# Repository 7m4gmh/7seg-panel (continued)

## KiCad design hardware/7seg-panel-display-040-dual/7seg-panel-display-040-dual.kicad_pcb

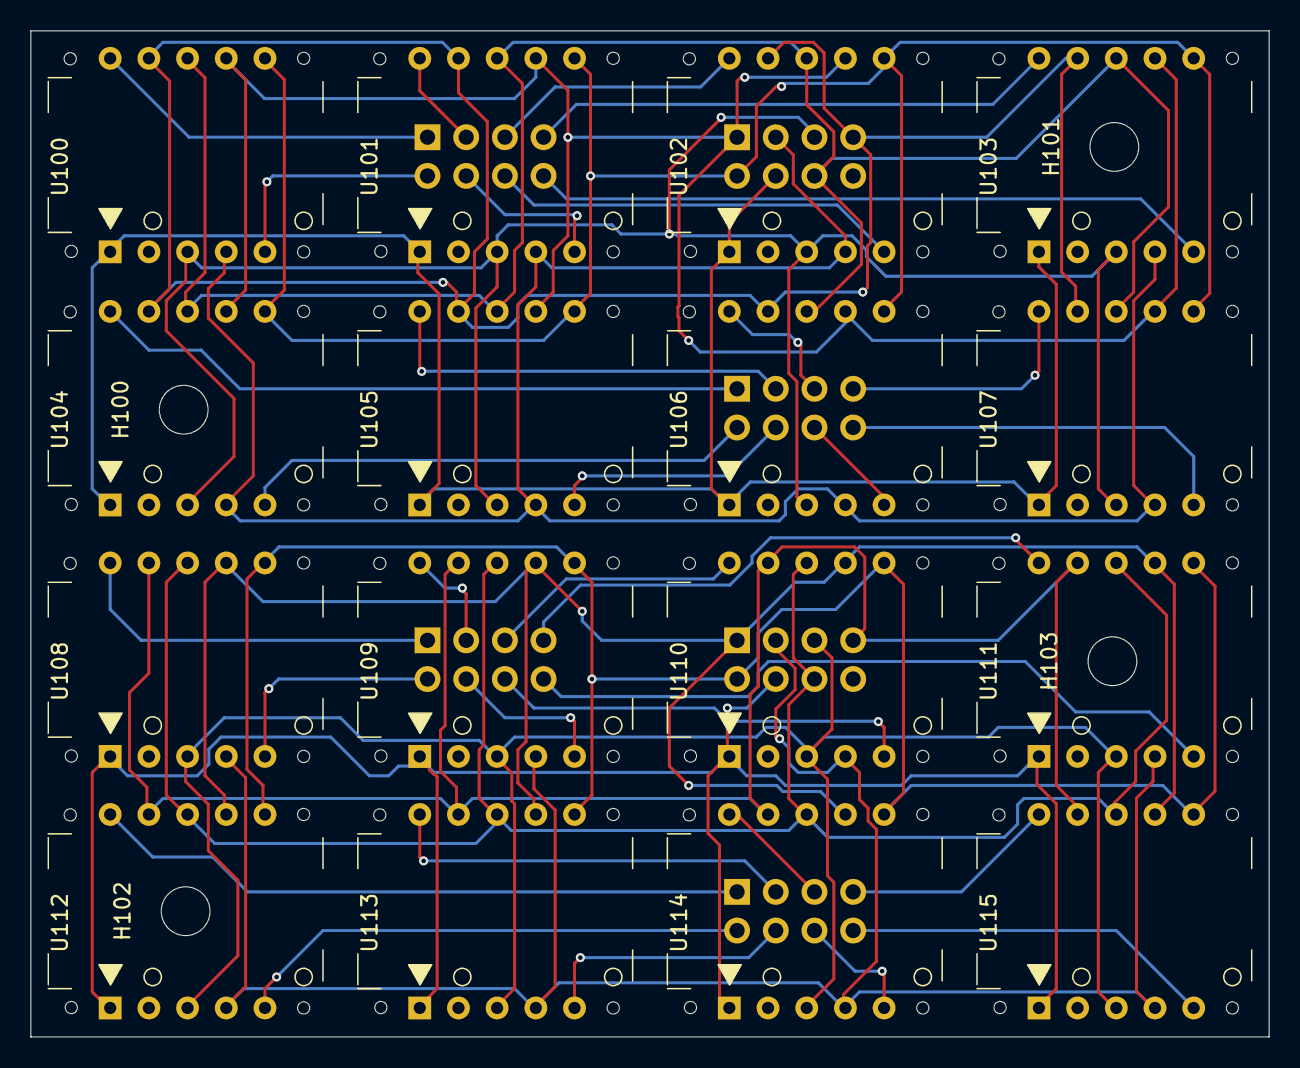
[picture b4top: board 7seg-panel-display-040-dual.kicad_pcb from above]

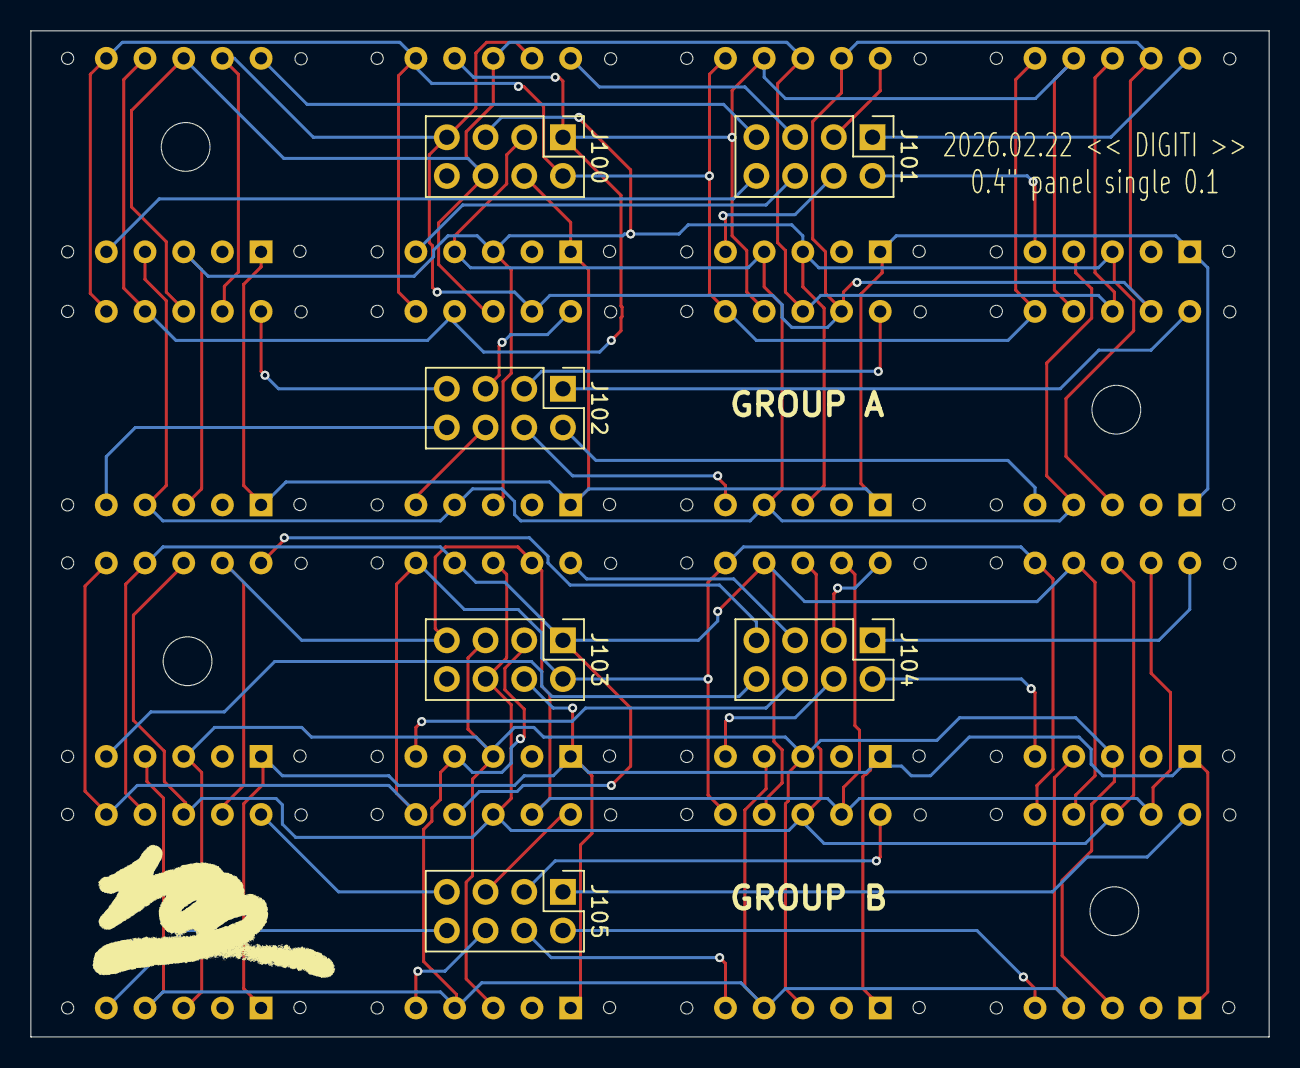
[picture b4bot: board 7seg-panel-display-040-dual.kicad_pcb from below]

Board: 2 copper layers, 81.3 x 66.0 mm, 26 parts (6 on the bottom side), 46 nets.

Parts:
H100, H101, H102, H103: MountingHole; MountingHole_3.2mm_M3
J100, J101, J102, J103, J104, J105: Conn_02x04_Odd_Even; PinHeader_2x04_P2.54mm_Vertical
U100, U101, U102, U103, U104, U105, U106, U107, U108, U109, U110, U111, U112, U113, U114, U115: YH-2E20402-IK; YH-2E20402-12P

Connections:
A_COM0: J100.1, U100.7 (a), U101.7 (a), U102.7 (a), U103.7 (a), U104.7 (a), U105.7 (a), U106.7 (a), U107.7 (a)
A_COM1: J100.2, U100.6 (b), U101.6 (b), U102.6 (b), U103.6 (b), U104.6 (b), U105.6 (b), U106.6 (b), U107.6 (b)
A_COM2: J100.3, U100.4 (c), U101.4 (c), U102.4 (c), U103.4 (c), U104.4 (c), U105.4 (c), U106.4 (c), U107.4 (c)
A_COM3: J100.4, U100.1 (d), U101.1 (d), U102.1 (d), U103.1 (d), U104.1 (d), U105.1 (d), U106.1 (d), U107.1 (d)
A_COM4: J100.5, U100.3 (e), U101.3 (e), U102.3 (e), U103.3 (e), U104.3 (e), U105.3 (e), U106.3 (e), U107.3 (e)
A_COM5: J100.6, U100.8 (f), U101.8 (f), U102.8 (f), U103.8 (f), U104.8 (f), U105.8 (f), U106.8 (f), U107.8 (f)
A_COM6: J100.7, U100.9 (g), U101.9 (g), U102.9 (g), U103.9 (g), U104.9 (g), U105.9 (g), U106.9 (g), U107.9 (g)
A_ROW0: J101.1, U100.10 (CA_D1)
A_ROW1: J101.2, U100.5 (CA_D2)
A_ROW2: J101.3, U101.10 (CA_D1)
A_ROW3: J101.4, U101.5 (CA_D2)
A_ROW4: J101.5, U102.10 (CA_D1)
A_ROW5: J101.6, U102.5 (CA_D2)
A_ROW6: J101.7, U103.10 (CA_D1)
A_ROW7: J101.8, U103.5 (CA_D2)
A_ROW8: J102.1, U104.10 (CA_D1)
A_ROW9: J102.2, U104.5 (CA_D2)
A_ROW10: J102.3, U105.10 (CA_D1)
A_ROW11: J102.4, U105.5 (CA_D2)
A_ROW12: J102.5, U106.10 (CA_D1)
A_ROW13: J102.6, U106.5 (CA_D2)
A_ROW14: J102.7, U107.10 (CA_D1)
A_ROW15: J102.8, U107.5 (CA_D2)
B_COM0: J103.1, U108.7 (a), U109.7 (a), U110.7 (a), U111.7 (a), U112.7 (a), U113.7 (a), U114.7 (a), U115.7 (a)
B_COM1: J103.2, U108.6 (b), U109.6 (b), U110.6 (b), U111.6 (b), U112.6 (b), U113.6 (b), U114.6 (b), U115.6 (b)
B_COM2: J103.3, U108.4 (c), U109.4 (c), U110.4 (c), U111.4 (c), U112.4 (c), U113.4 (c), U114.4 (c), U115.4 (c)
B_COM3: J103.4, U108.1 (d), U109.1 (d), U110.1 (d), U111.1 (d), U112.1 (d), U113.1 (d), U114.1 (d), U115.1 (d)
B_COM4: J103.5, U108.3 (e), U109.3 (e), U110.3 (e), U111.3 (e), U112.3 (e), U113.3 (e), U114.3 (e), U115.3 (e)
B_COM5: J103.6, U108.8 (f), U109.8 (f), U110.8 (f), U111.8 (f), U112.8 (f), U113.8 (f), U114.8 (f), U115.8 (f)
B_COM6: J103.7, U108.9 (g), U109.9 (g), U110.9 (g), U111.9 (g), U112.9 (g), U113.9 (g), U114.9 (g), U115.9 (g)
B_ROW0: J104.1, U108.10 (CA_D1)
B_ROW1: J104.2, U108.5 (CA_D2)
B_ROW2: J104.3, U109.10 (CA_D1)
B_ROW3: J104.4, U109.5 (CA_D2)
B_ROW4: J104.5, U110.10 (CA_D1)
B_ROW5: J104.6, U110.5 (CA_D2)
B_ROW6: J104.7, U111.10 (CA_D1)
B_ROW7: J104.8, U111.5 (CA_D2)
B_ROW8: J105.1, U112.10 (CA_D1)
B_ROW9: J105.2, U112.5 (CA_D2)
B_ROW10: J105.3, U113.10 (CA_D1)
B_ROW11: J105.4, U113.5 (CA_D2)
B_ROW12: J105.5, U114.10 (CA_D1)
B_ROW13: J105.6, U114.5 (CA_D2)
B_ROW14: J105.7, U115.10 (CA_D1)
B_ROW15: J105.8, U115.5 (CA_D2)

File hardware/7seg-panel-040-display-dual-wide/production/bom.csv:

Designator,Footprint,Quantity,Value,LCSC Part #
"J100, J101, J102, J103, J104, J105",PinHeader_2x04_P2.54mm_Vertical,6,Conn_02x04_Odd_Even,
"U100, U101, U102, U103, U104, U105, U106, U107, U108, U109, U110, U111, U112, U113, U114, U115",YH-2E20402-12P,16,YH-2E20402-IK,

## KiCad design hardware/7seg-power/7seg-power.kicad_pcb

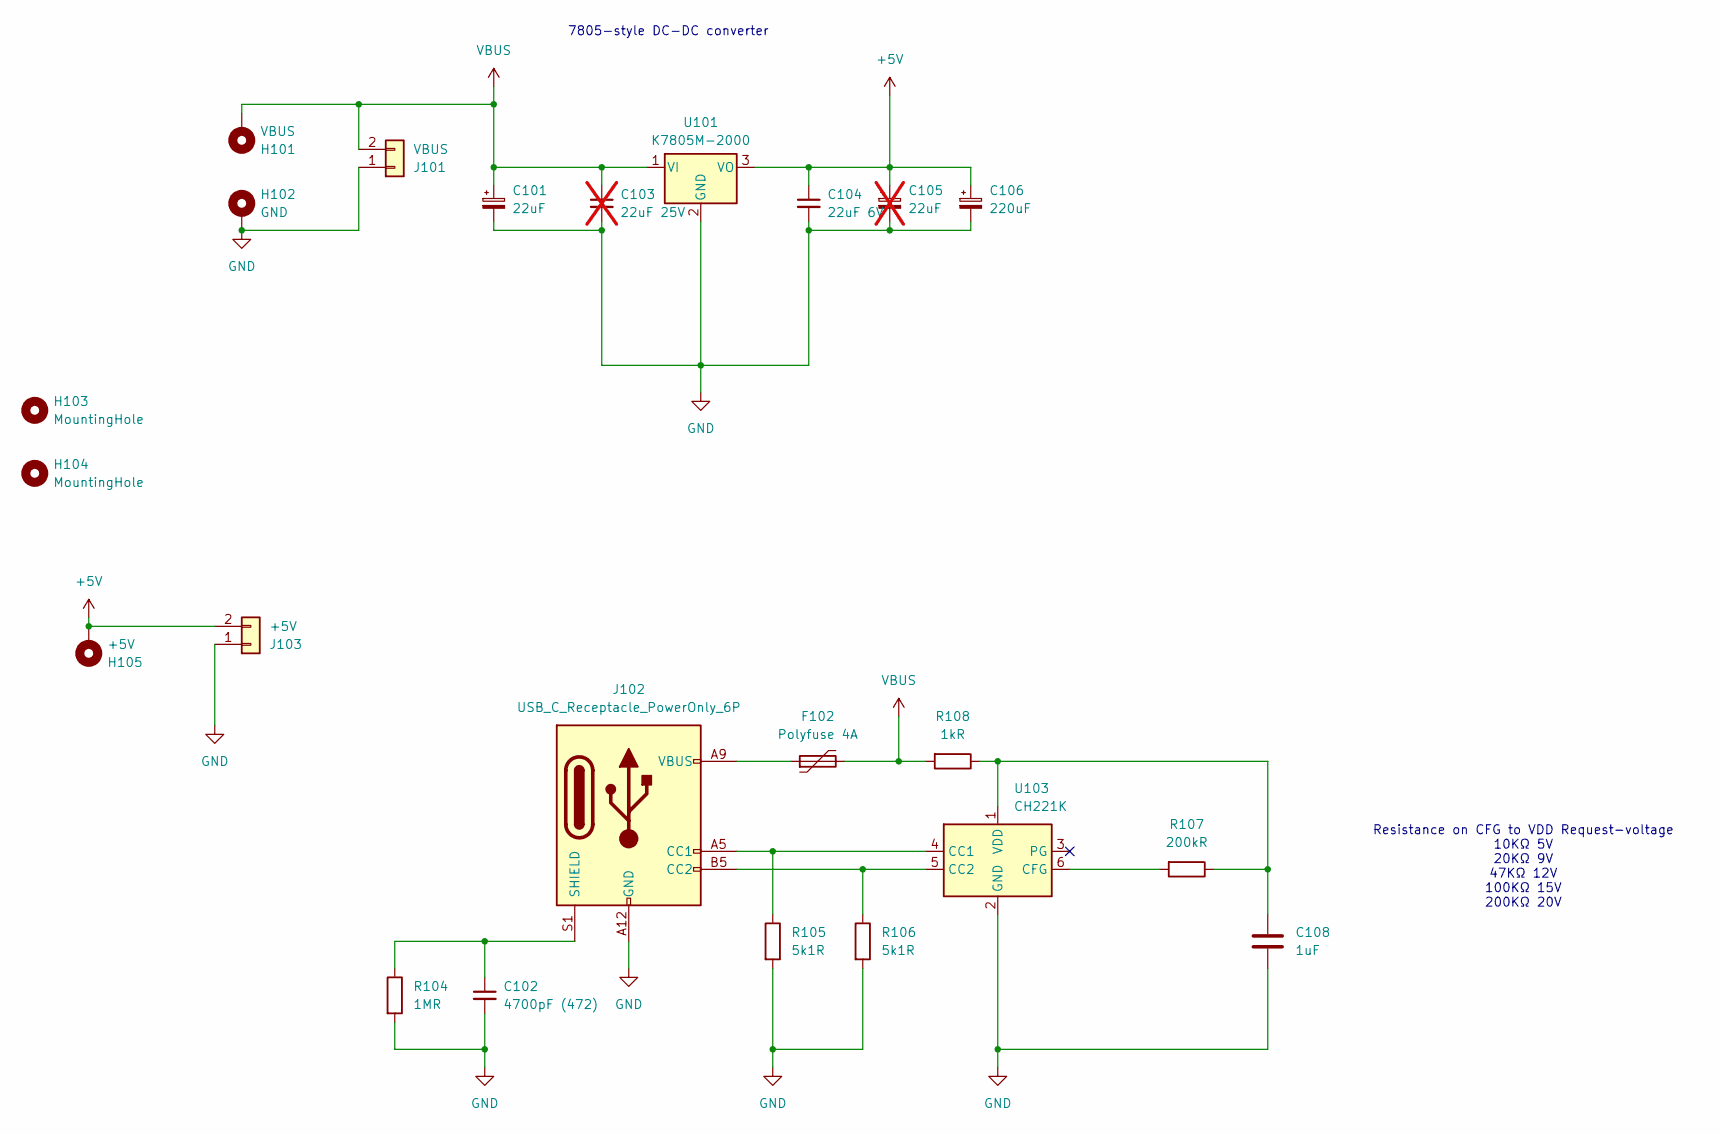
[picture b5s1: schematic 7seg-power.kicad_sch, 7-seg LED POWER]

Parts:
C101: 22uF; CP_EIA-3528-21_Kemet-B
C102: 4700pF (472); C_0805_2012Metric_Pad1.18x1.45mm_HandSolder
C103: 22uF 25V; C_0603_1608Metric_Pad1.08x0.95mm_HandSolder; not fitted
C104: 22uF 6V; C_0603_1608Metric_Pad1.08x0.95mm_HandSolder
C105: 22uF; CP_EIA-3528-21_Kemet-B; not fitted
C106: 220uF; C_Elec_6.3x5.8
C108: 1uF; C_0805_2012Metric_Pad1.18x1.45mm_HandSolder
F102: Polyfuse 4A; Fuse_2920_7451Metric_Pad2.10x5.45mm_HandSolder
H101: VBUS; MountingHole_3.2mm_M3_DIN965_Pad
H102: GND; MountingHole_3.2mm_M3_DIN965_Pad
H103, H104: MountingHole; MountingHole_3.2mm_M3
H105: +5V; MountingHole_3.2mm_M3_DIN965_Pad
J101: VBUS; Generic_XH_S2B-XH-A-1_1x02_P2.50mm_Horizontal
J102: USB_C_Receptacle_PowerOnly_6P; USB_C_Receptacle_GCT_USB4125-xx-x-0190_6P_TopMnt_Horizontal
J103: +5V; Generic_XH_S2B-XH-A-1_1x02_P2.50mm_Horizontal
R104: 1MR; R_0805_2012Metric_Pad1.20x1.40mm_HandSolder
R105, R106: 5k1R; R_0805_2012Metric_Pad1.20x1.40mm_HandSolder
R107: 200kR; R_0805_2012Metric_Pad1.20x1.40mm_HandSolder
R108: 1kR; R_1210_3225Metric_Pad1.30x2.65mm_HandSolder
U101: K7805M-2000; TO-220-3_Vertical
U103: CH221K; TSOT-23-6_HandSoldering

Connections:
+5V: C104.1, C105.1, C106.1, H105.1 (MP), J103.2, U101.3 (VO)
GND: C101.2, C102.2, C103.2, C104.2, C105.2, C106.2, C108.2, H102.1 (MP), J101.1, J102.A12 (GND), J102.B12 (GND), J103.1, R104.2, R105.2, R106.2, U101.2 (GND), U103.2 (GND)
unnamed: F102.1, J102.A9 (VBUS), J102.B9 (VBUS)
unnamed: J102.A5 (CC1), R105.1, U103.4 (CC1)
unnamed: J102.B5 (CC2), R106.1, U103.5 (CC2)
unnamed: C102.1, J102.S1 (SHIELD), R104.1
unnamed: R107.2, U103.6 (CFG)
unnamed: C108.1, R107.1, R108.1, U103.1 (VDD)
VBUS: C101.1, C103.1, F102.2, H101.1 (MP), J101.2, R108.2, U101.1 (VI)

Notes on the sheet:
7805-style DC-DC converter
Resistance on CFG to VDD Request-voltage 10KΩ 5V 20KΩ 9V 47KΩ 12V 100KΩ 15V 200KΩ 20V

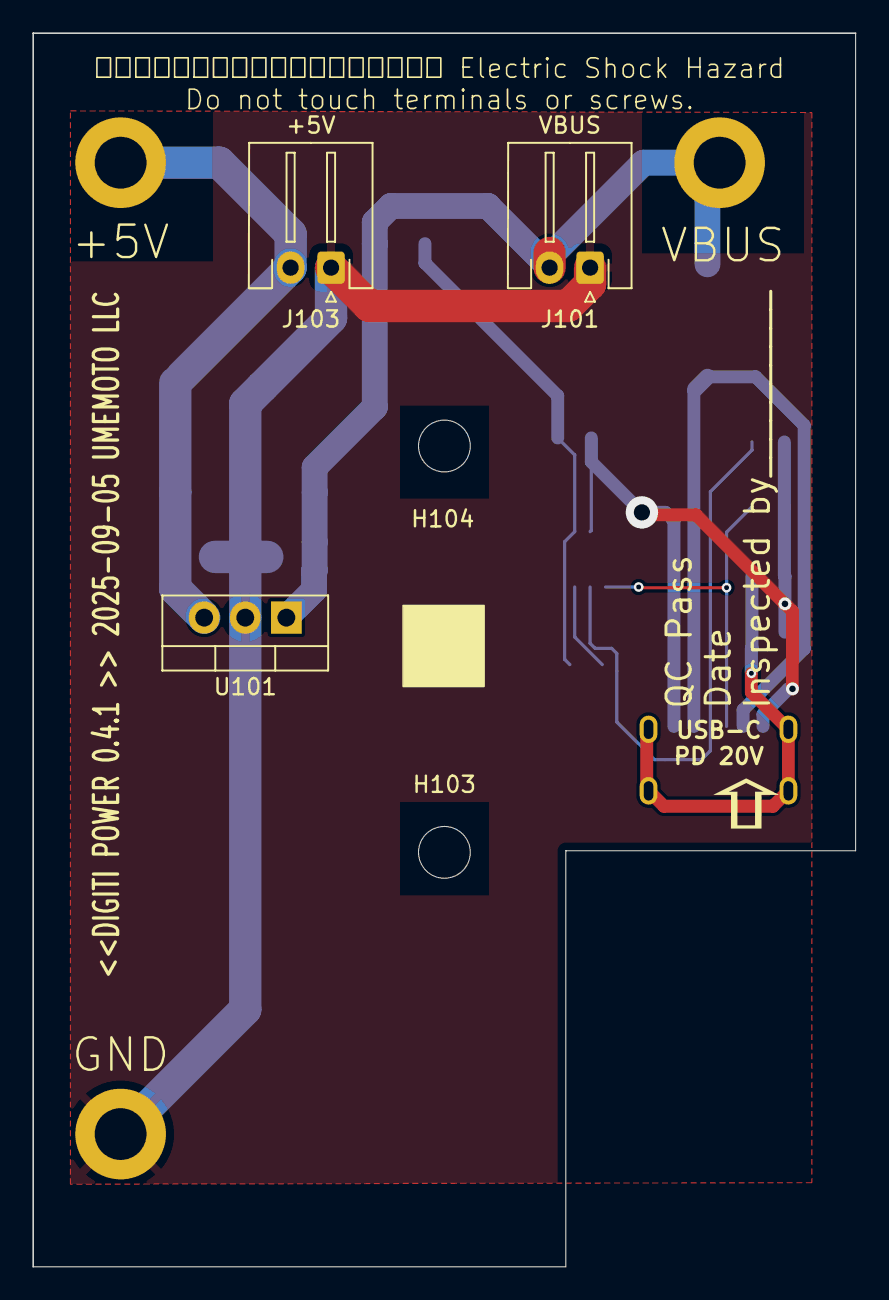
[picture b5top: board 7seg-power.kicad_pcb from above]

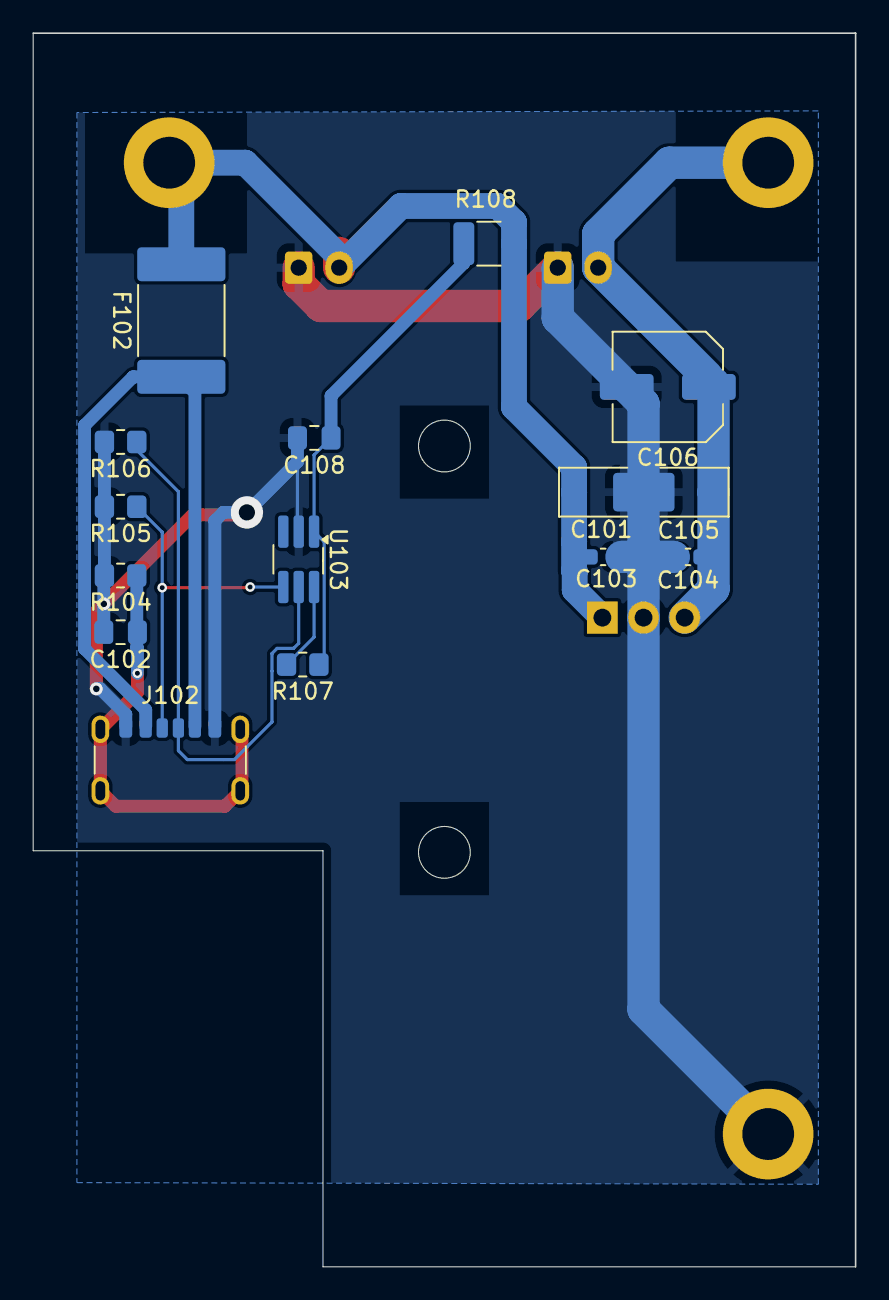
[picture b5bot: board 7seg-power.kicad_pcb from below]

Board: 2 copper layers, 50.8 x 76.2 mm, 23 parts (15 on the bottom side), 9 nets.

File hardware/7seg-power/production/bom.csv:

Designator,Footprint,Quantity,Value,LCSC Part #
C101,CP_EIA-3528-21_Kemet-B,1,22uF,
C102,0805,1,4700pF (472),
C104,0603,1,22uF 6V,
C106,C_Elec_6.3x5.8,1,220uF,
C108,0805,1,1uF,
F102,2920,1,Polyfuse 4A,
J101,Generic_XH_S2B-XH-A-1_1x02_P2.50mm_Horizontal,1,VBUS,
J102,USB_C_Receptacle_GCT_USB4125-xx-x-0190_6P_TopMnt_Horizontal,1,USB_C_Receptacle_PowerOnly_6P,
J103,Generic_XH_S2B-XH-A-1_1x02_P2.50mm_Horizontal,1,+5V,
R104,0805,1,1MR,
"R105, R106",0805,2,5k1R,
R107,0805,1,200kR,
R108,1210,1,1kR,
U101,TO-220-3_Vertical,1,K7805M-2000,
U103,TSOT-23-6_HandSoldering,1,CH221K,
